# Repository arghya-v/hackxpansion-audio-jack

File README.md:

# Hackxpansion Audio Jack
This project adds stereo audio playback through a **TLV320DAC3100** DAC and a **3.5 mm headphone jack**, along with physical controls for playback.
<br/>
**Crates**: pkg:cargo/audio_jack_firmware@0.1.0
## Images

## Schematic

### Audio Module

| GPIO  | Function         |
| ----- | ---------------- |
| GPIO0 | I²C SCL          |
| GPIO1 | I²C SDA          |
| GPIO2 | I²S BCLK         |
| GPIO3 | I²S DIN          |
| GPIO4 | I²S WCLK / LRCLK |
| GPIO5 | DAC MCLK         |
| GPIO6 | DAC RESET        |
| GPIO7 | Next             |
| GPIO8 | Previous         |
| GPIO9 | Play / Pause     |

See the [Xpanse API docs](https://docs.rs/xpanse-api/latest/xpanse_api/index.html)

---

This was all possible thanks to [Hackspansion: A hackclub YSWS](http://hackxpansion.hackclub.com/)

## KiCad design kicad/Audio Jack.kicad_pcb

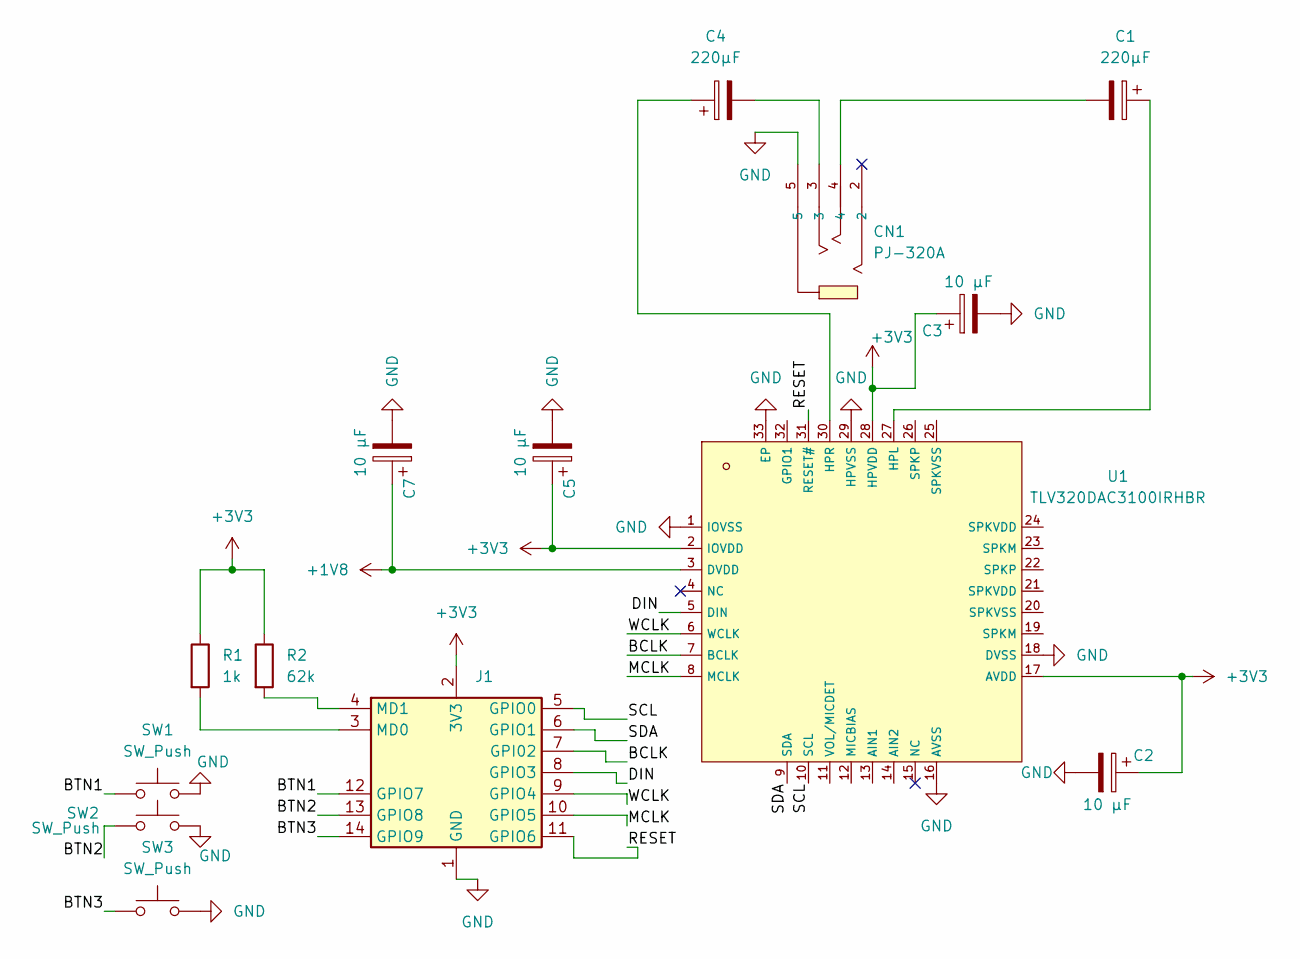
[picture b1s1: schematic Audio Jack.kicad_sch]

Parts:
C1, C4: 220µF; C469553_C1210
C2, C3, C5, C7: 10 µF; C15850_C0805
CN1: PJ-320A; C2884926_AUDIO-TH_XKB_PJ-320A; LCSC C2884926
J1: Male_Module
R1: 1k; R_0805_2012Metric_Pad1.20x1.40mm_HandSolder
R2: 62k; R_0805_2012Metric_Pad1.20x1.40mm_HandSolder
SW1, SW2, SW3: SW_Push; SW_PUSH_6mm
U1: TLV320DAC3100IRHBR; C179677_LFCSP-32_L5_0-W5_0-P0_50-BL-EP; LCSC C179677

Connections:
+1V8: C7.1, U1.3 (DVDD)
+3V3: C2.1, C3.1, C5.1, J1.2 (3V3), R1.1, R2.1, U1.2 (IOVDD), U1.17 (AVDD), U1.28 (HPVDD)
/BCLK: J1.7 (GPI02), U1.7 (BCLK)
/BTN1: J1.12 (GPIO7), SW1.1
/BTN2: J1.13 (GPIO8), SW2.1
/BTN3: J1.14 (GPIO9), SW3.1
/DIN: J1.8 (GPIO3), U1.5 (DIN)
/MCLK: J1.10 (GPIO5), U1.8 (MCLK)
/RESET: J1.11 (GPIO6), U1.31 (RESET#)
/SCL: J1.5 (GPIO0), U1.10 (SCL)
/SDA: J1.6 (GPIO1), U1.9 (SDA)
/WCLK: J1.9 (GPIO4), U1.6 (WCLK)
GND: C2.2, C3.2, C5.2, C7.2, CN1.5, J1.1 (GND), SW1.2, SW2.2, SW3.2, U1.1 (IOVSS), U1.16 (AVSS), U1.18 (DVSS), U1.29 (HPVSS), U1.33 (EP)
unnamed: C1.2, CN1.4
unnamed: C4.2, CN1.3
unnamed: J1.3 (MD0), R1.2
unnamed: J1.4 (MD1), R2.2
unnamed: C1.1, U1.27 (HPL)
unnamed: C4.1, U1.30 (HPR)

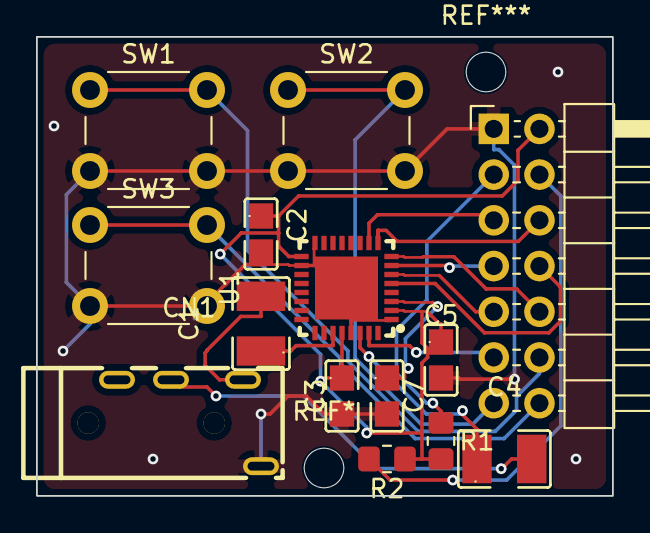
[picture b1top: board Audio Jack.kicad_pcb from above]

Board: 2 copper layers, 32.0 x 25.5 mm, 14 parts (0 on the bottom side), 19 nets.

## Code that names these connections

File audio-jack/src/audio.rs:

use embassy_rp::{
    dma,
    gpio::{Level, Output},
    interrupt::typelevel::{Binding, DMA_IRQ_0},
    peripherals::DMA_CH0,
    pio_programs::{
        clk::{PioClk, PioClkProgram},
        i2s::{PioI2sOut, PioI2sOutProgram},
    },
};

use embedded_hal_async::i2c::I2c;

use xpanse_api::{
    with_pio,
    bus::allocator::BusAllocator,
    driver::{Driver, DriverError, DriverMeta},
    gpio_bank::{BankPins, GpioBank},
    interfaces::buttons::{
        pin_button,
        A,
        B,
        X,
    },
    metadata::{ModuleDetectResistor, ModuleID, ModuleSlot},
    registry::Registry,
};

const DAC_ADDRESS: u8 = 0x18;

const SAMPLE_RATE: u32 = 48_000;
const BIT_DEPTH: u32 = 16;
const MCLK_FREQUENCY: u32 = 12_288_000;

#[derive(Copy, Clone)]
pub struct AudioDmaIrqs;

unsafe impl Binding<DMA_IRQ_0, dma::InterruptHandler<DMA_CH0>> for AudioDmaIrqs {}

pub struct AudioDriver;

impl DriverMeta for AudioDriver {
    const ID: ModuleID = ModuleID {
        md0: ModuleDetectResistor::R1K,
        md1: ModuleDetectResistor::R62K,
    };
}

impl<G> Driver<G> for AudioDriver
where
    G: BankPins,
{
    async fn create(
        bank: GpioBank<G>,
        slot: ModuleSlot,
        registry: &mut Registry,
        buses: &mut BusAllocator,
    ) -> Result<(), DriverError> {
        // RESET
        let mut reset = Output::new(
            bank.gpio6,
            Level::Low,
        );

        embassy_time::Timer::after_millis(5).await;

        reset.set_high();

        embassy_time::Timer::after_millis(10).await;

        core::mem::forget(reset);

        // I2C
        let mut i2c_bus = buses
            .create_i2c_bitbang(
                bank.gpio0,
                bank.gpio1,
                400_000,
            )
            .map_err(|_| DriverError::InitFailed)?;

        // DAC SOFTWARE RESET
        dac_write(
            &mut i2c_bus,
            0x00,
            0x01,
        )
        .await?;

        embassy_time::Timer::after_millis(10).await;

        // DAC CONFIGURATION
        configure_dac(&mut i2c_bus).await?;

        // BUTTONS
        registry.register(
            slot,
            Self::ID,
            pin_button::<A>(bank.gpio7.into()),
        );

        registry.register(
            slot,
            Self::ID,
            pin_button::<B>(bank.gpio8.into()),
        );

        registry.register(
            slot,
            Self::ID,
            pin_button::<X>(bank.gpio9.into()),
        );

        // DMA
        let dma = buses
            .request_dma::<DMA_CH0>()
            .map_err(|_| DriverError::InitFailed)?;

        // MCLK
        let mclk_pio = buses
            .request_pio(&[
                &bank.gpio5,
            ])
            .ok_or(DriverError::InitFailed)?;

        with_pio!(
            mclk_pio,
            mclk_common,
            mclk_sm,
            {
                let mclk_program = PioClkProgram::new(
                    &mut *mclk_common,
                );

                let mut mclk = PioClk::new(
                    &mut *mclk_common,
                    mclk_sm,
                    bank.gpio5,
                    &mclk_program,
                    MCLK_FREQUENCY,
                );

                mclk.start();

                core::mem::forget(mclk);
            }
        );

        // I2S
        let i2s_pio = buses
            .request_pio(&[
                &bank.gpio2,
                &bank.gpio3,
                &bank.gpio4,
            ])
            .ok_or(DriverError::InitFailed)?;

        with_pio!(
            i2s_pio,
            i2s_common,
            i2s_sm,
            {
                let i2s_program = PioI2sOutProgram::new(
                    &mut *i2s_common,
                );

                let mut i2s = PioI2sOut::new(
                    &mut *i2s_common,
                    i2s_sm,
                    dma,
                    AudioDmaIrqs,
                    bank.gpio3, // DIN
                    bank.gpio2, // BCLK
                    bank.gpio4, // LRCLK
                    SAMPLE_RATE,
                    BIT_DEPTH,
                    &i2s_program,
                );

                i2s.start();

                // Register I2S so applications can acquire it
                // and call i2s.write(samples).await.
                registry.register(
                    slot,
                    Self::ID,
                    i2s,
                );
            }
        );

        Ok(())
    }
}

async fn dac_write<I>(
    i2c: &mut I,
    register: u8,
    value: u8,
) -> Result<(), DriverError>
where
    I: I2c,
{
    i2c.write(
        DAC_ADDRESS,
        &[register, value],
    )
    .await
    .map_err(|_| DriverError::InitFailed)
}

async fn configure_dac<I>(
    i2c: &mut I,
) -> Result<(), DriverError>
where
    I: I2c,
{
    // CODEC_CLKIN = MCLK
    dac_write(i2c, 0x00, 0x00).await?;
    dac_write(i2c, 0x04, 0x00).await?;

    // NDAC = 8, powered
    dac_write(i2c, 0x0B, 0x88).await?;

    // MDAC = 2, powered
    dac_write(i2c, 0x0C, 0x82).await?;

    // DOSR = 128
    dac_write(i2c, 0x0D, 0x00).await?;
    dac_write(i2c, 0x0E, 0x80).await?;

    // I2S, 16-bit, codec slave
    dac_write(i2c, 0x1B, 0x00).await?;

    // Page 1
    dac_write(i2c, 0x00, 0x01).await?;

    // Common-mode voltage
    dac_write(i2c, 0x1F, 0x04).await?;

    // De-pop
    dac_write(i2c, 0x21, 0x4E).await?;

    // LDAC -> HPL
    // RDAC -> HPR
    dac_write(i2c, 0x23, 0x44).await?;

    // HPL unmuted
    dac_write(i2c, 0x28, 0x06).await?;

    // HPR unmuted
    dac_write(i2c, 0x29, 0x06).await?;

    // Power HPL + HPR
    dac_write(i2c, 0x1F, 0xC2).await?;

    // Analog output volume = -9 dB
    dac_write(i2c, 0x24, 0x92).await?;
    dac_write(i2c, 0x25, 0x92).await?;

    // Page 0
    dac_write(i2c, 0x00, 0x00).await?;

    // Power DAC L/R + soft stepping
    dac_write(i2c, 0x3F, 0xD4).await?;

    // Digital gain
    dac_write(i2c, 0x41, 0xD4).await?;
    dac_write(i2c, 0x42, 0xD4).await?;

    // Unmute DAC
    dac_write(i2c, 0x40, 0x00).await?;

    Ok(())
}
